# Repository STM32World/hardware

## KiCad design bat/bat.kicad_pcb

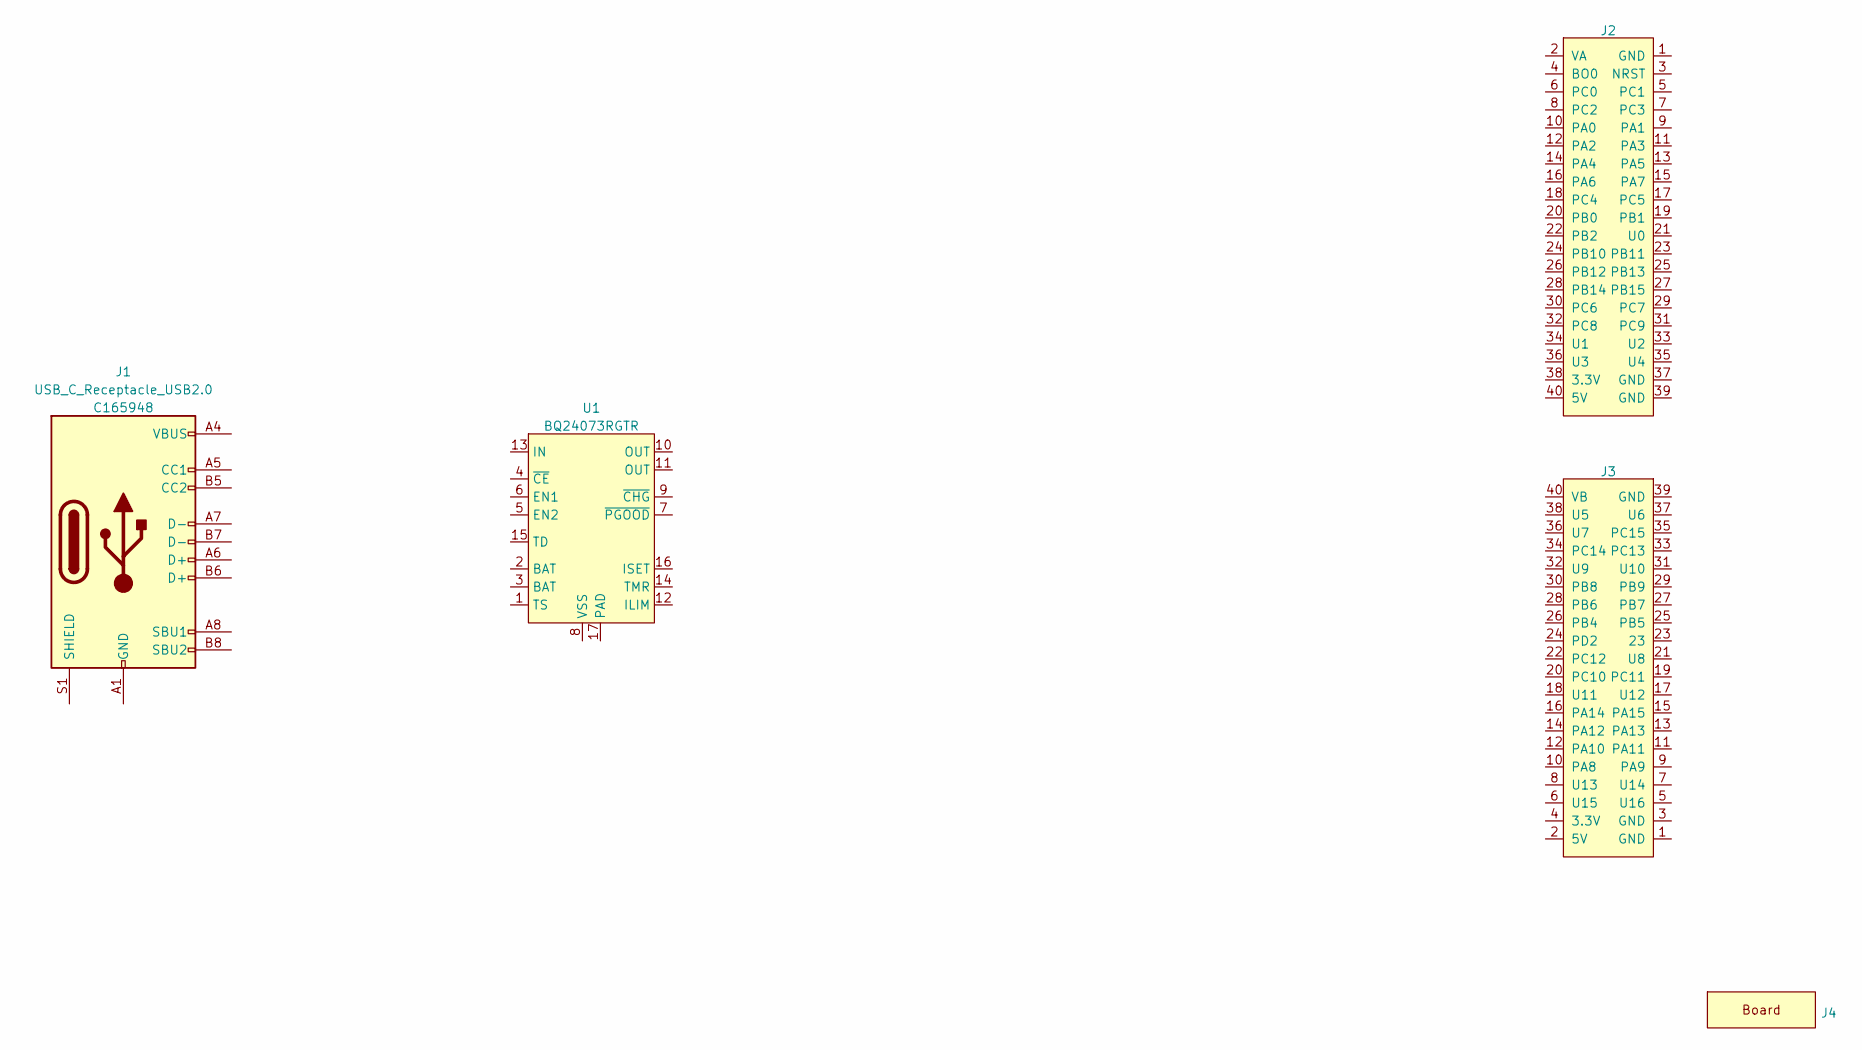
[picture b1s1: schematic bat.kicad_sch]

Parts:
J1: USB_C_Receptacle_USB2.0; USB_C_Receptacle_HRO_TYPE-C-31-M-12; LCSC C165948
J2: STM32WORLD_CONNECTOR_1; PinSocket_2x20_P2.54mm_Vertical_Stackable; LCSC C35165
J3: STM32WORLD_CONNECTOR_2; PinSocket_2x20_P2.54mm_Vertical_Stackable; LCSC C35165
J4: STM32WORLD_BOARD
U1: BQ24073RGTR; QFN-16-1EP_3x3mm_P0.5mm_EP1.7x1.7mm; LCSC C15220

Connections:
unnamed: J1.A1 (GND), J1.A12 (GND), J1.B1 (GND), J1.B12 (GND)
unnamed: J1.A4 (VBUS), J1.A9 (VBUS), J1.B4 (VBUS), J1.B9 (VBUS)

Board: 2 copper layers, 5 parts (0 on the bottom side), 2 nets, no tracks yet.

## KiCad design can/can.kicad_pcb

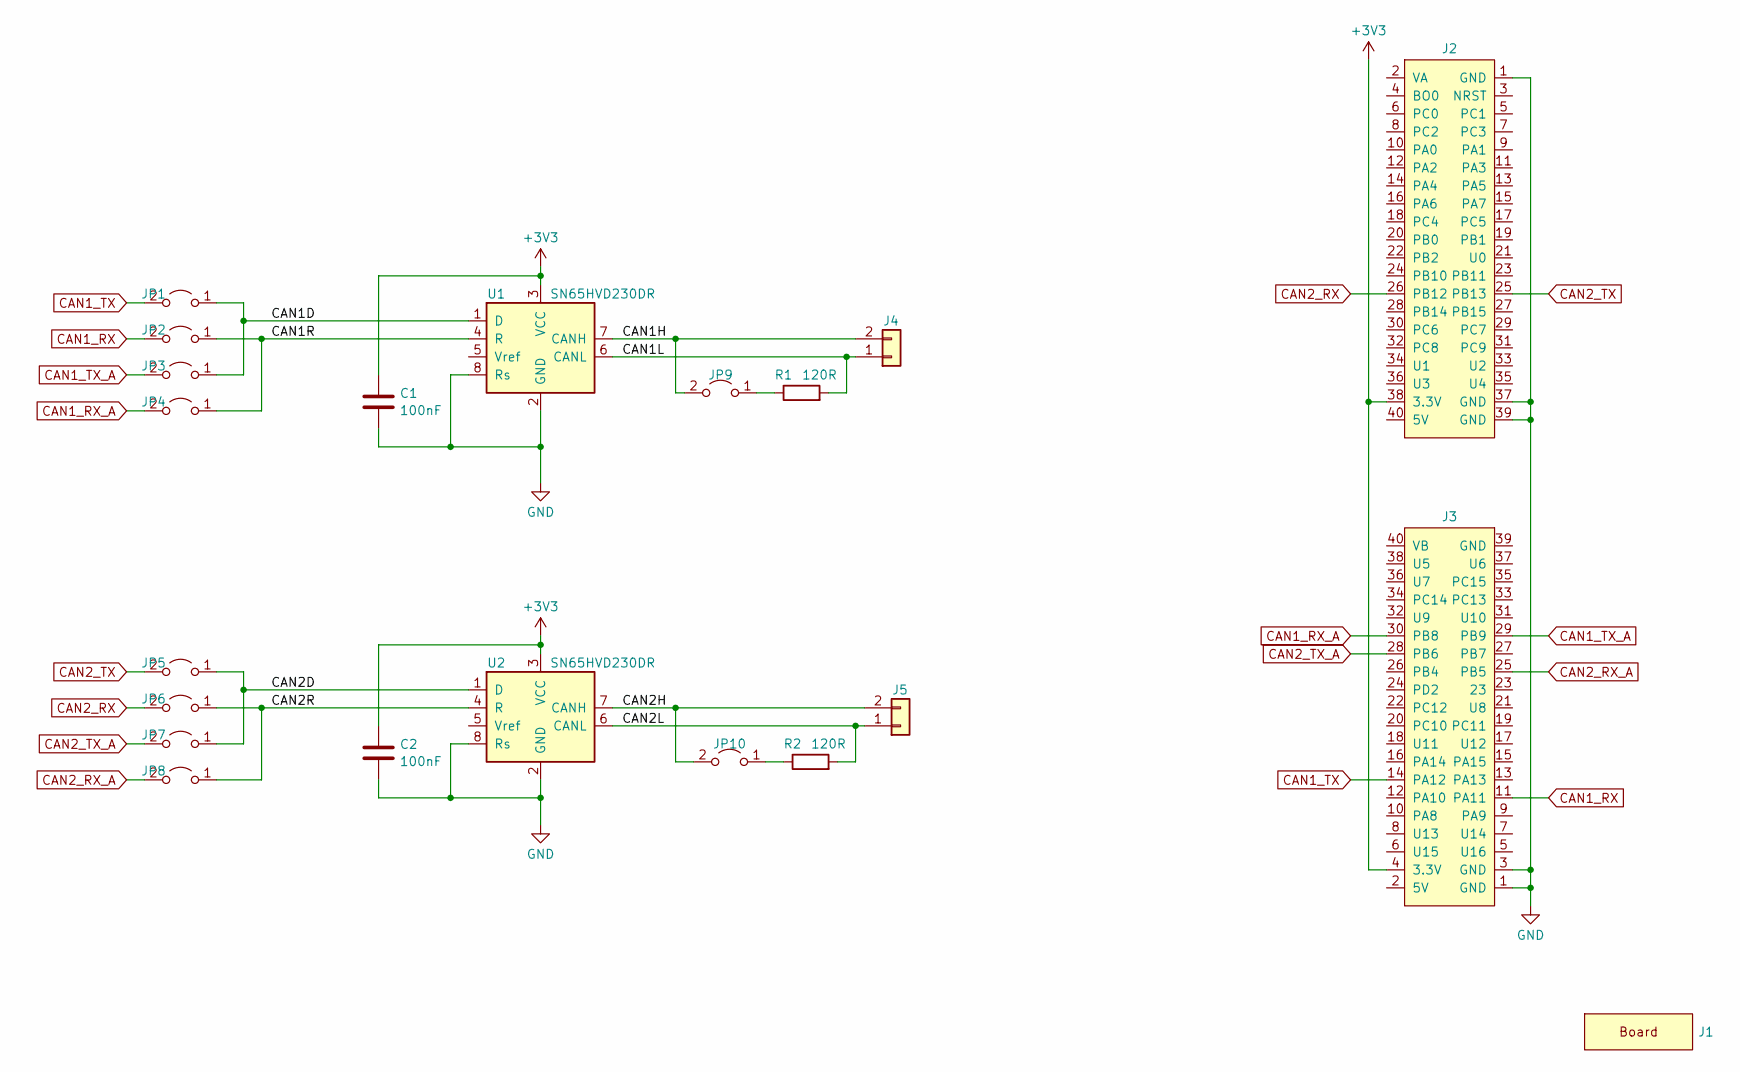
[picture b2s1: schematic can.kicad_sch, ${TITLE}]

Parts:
C1, C2: 100nF; C_0603_1608Metric; LCSC C14663
J1: STM32WORLD_BOARD
J2: STM32WORLD_CONNECTOR_1; PinSocket_2x20_P2.54mm_Vertical_Stackable; LCSC C35165
J3: STM32WORLD_CONNECTOR_2; PinSocket_2x20_P2.54mm_Vertical_Stackable; LCSC C35165
J4, J5: TerminalBlock_Phoenix_PT-1,5-2-5.0-H_1x02_P5.00mm_Horizontal
JP1, JP2, JP3, JP4, JP5, JP6, JP7, JP8, JP9, JP10: SolderJumper-2_P1.3mm_Open_TrianglePad1.0x1.5mm
R1, R2: 120R; R_0603_1608Metric; LCSC C22787
U1, U2: SN65HVD230DR; SOIC-8_3.9x4.9mm_P1.27mm; LCSC C12084

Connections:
+3V3: C1.1, C2.1, J2.38 (3.3V), J3.4 (3.3V), U1.3 (VCC), U2.3 (VCC)
/CAN1D: JP1.1 (A), JP3.1 (A), U1.1 (D)
/CAN1H: J4.2, JP9.2 (B), U1.7 (CANH)
/CAN1L: J4.1, R1.2, U1.6 (CANL)
/CAN1R: JP2.1 (A), JP4.1 (A), U1.4 (R)
/CAN2D: JP5.1 (A), JP7.1 (A), U2.1 (D)
/CAN2H: J5.2, JP10.2 (B), U2.7 (CANH)
/CAN2L: J5.1, R2.2, U2.6 (CANL)
/CAN2R: JP6.1 (A), JP8.1 (A), U2.4 (R)
CAN1_RX: J3.11 (PA11), JP2.2 (B)
CAN1_RX_A: J3.30 (PB8), JP4.2 (B)
CAN1_TX: J3.14 (PA12), JP1.2 (B)
CAN1_TX_A: J3.29 (PB9), JP3.2 (B)
CAN2_RX: J2.26 (PB12), JP6.2 (B)
CAN2_RX_A: J3.25 (PB5), JP8.2 (B)
CAN2_TX: J2.25 (PB13), JP5.2 (B)
CAN2_TX_A: J3.28 (PB6), JP7.2 (B)
GND: C1.2, C2.2, J2.1 (GND), J2.37 (GND), J2.39 (GND), J3.1 (GND), J3.3 (GND), U1.2 (GND), U1.8 (Rs), U2.2 (GND), U2.8 (Rs)
unnamed: JP9.1 (A), R1.1
unnamed: JP10.1 (A), R2.1

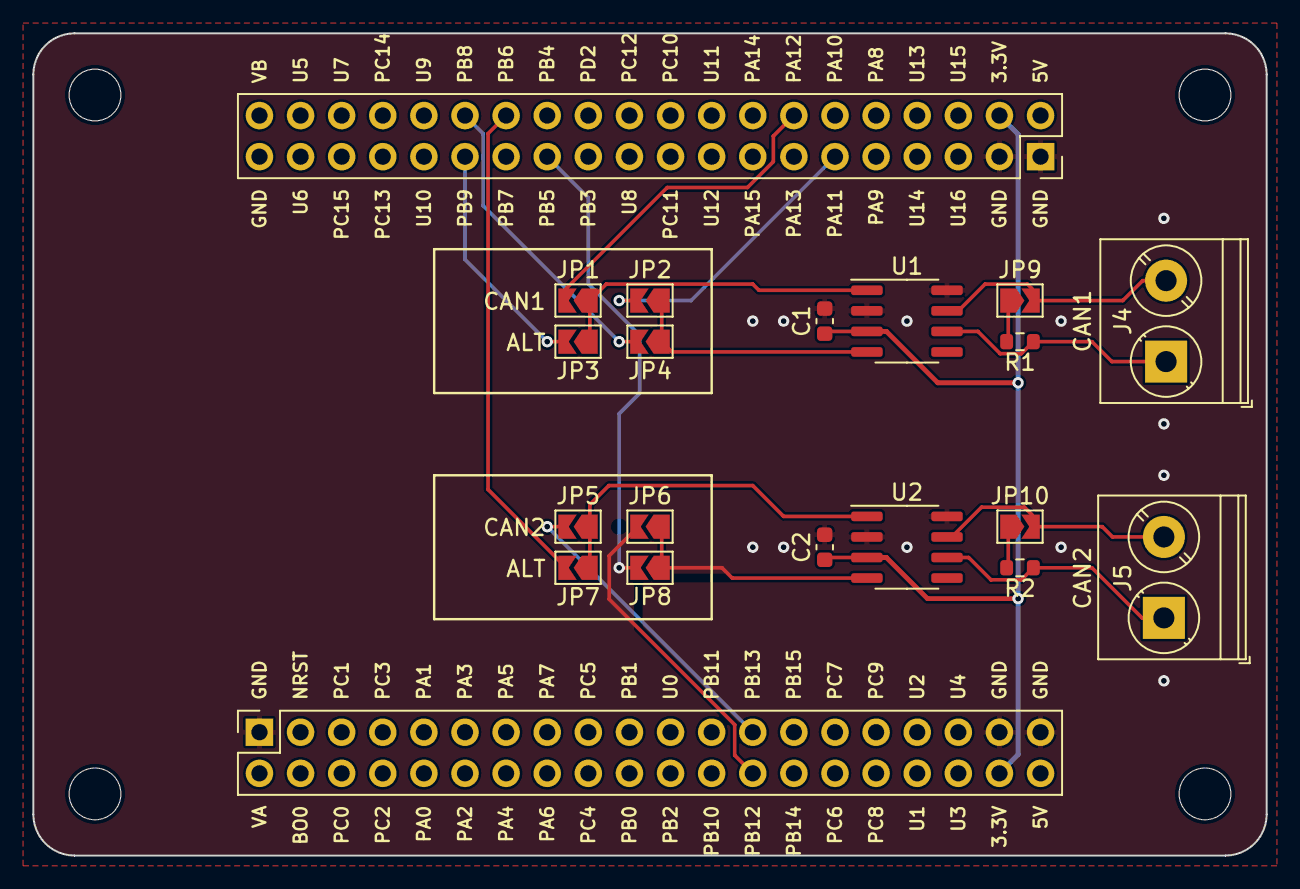
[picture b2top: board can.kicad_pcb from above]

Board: 2 copper layers, 76.2 x 50.8 mm, 21 parts (0 on the bottom side), 20 nets.

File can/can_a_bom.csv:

Comment,Designator,Footprint,LCSC
"100nF","C1,C2","Capacitor_SMD:C_0603_1608Metric","C14663"
"STM32WORLD_BOARD","J1","stm32world:STM32WORLD_BOARD"
"STM32WORLD_CONNECTOR_1","J2","stm32world:PinSocket_2x20_P2.54mm_Vertical_Stackable","C35165"
"STM32WORLD_CONNECTOR_2","J3","stm32world:PinSocket_2x20_P2.54mm_Vertical_Stackable","C35165"
"~","J4,J5","TerminalBlock_Phoenix:TerminalBlock_Phoenix_PT-1,5-2-5.0-H_1x02_P5.00mm_Horizontal"
"~","JP1,JP2,JP3,JP4,JP5,JP6,JP7,JP8,JP9,JP10","Jumper:SolderJumper-2_P1.3mm_Open_TrianglePad1.0x1.5mm"
"120R","R1,R2","Resistor_SMD:R_0603_1608Metric","C22787"
"SN65HVD230DR","U1,U2","Package_SO:SOIC-8_3.9x4.9mm_P1.27mm","C12084"

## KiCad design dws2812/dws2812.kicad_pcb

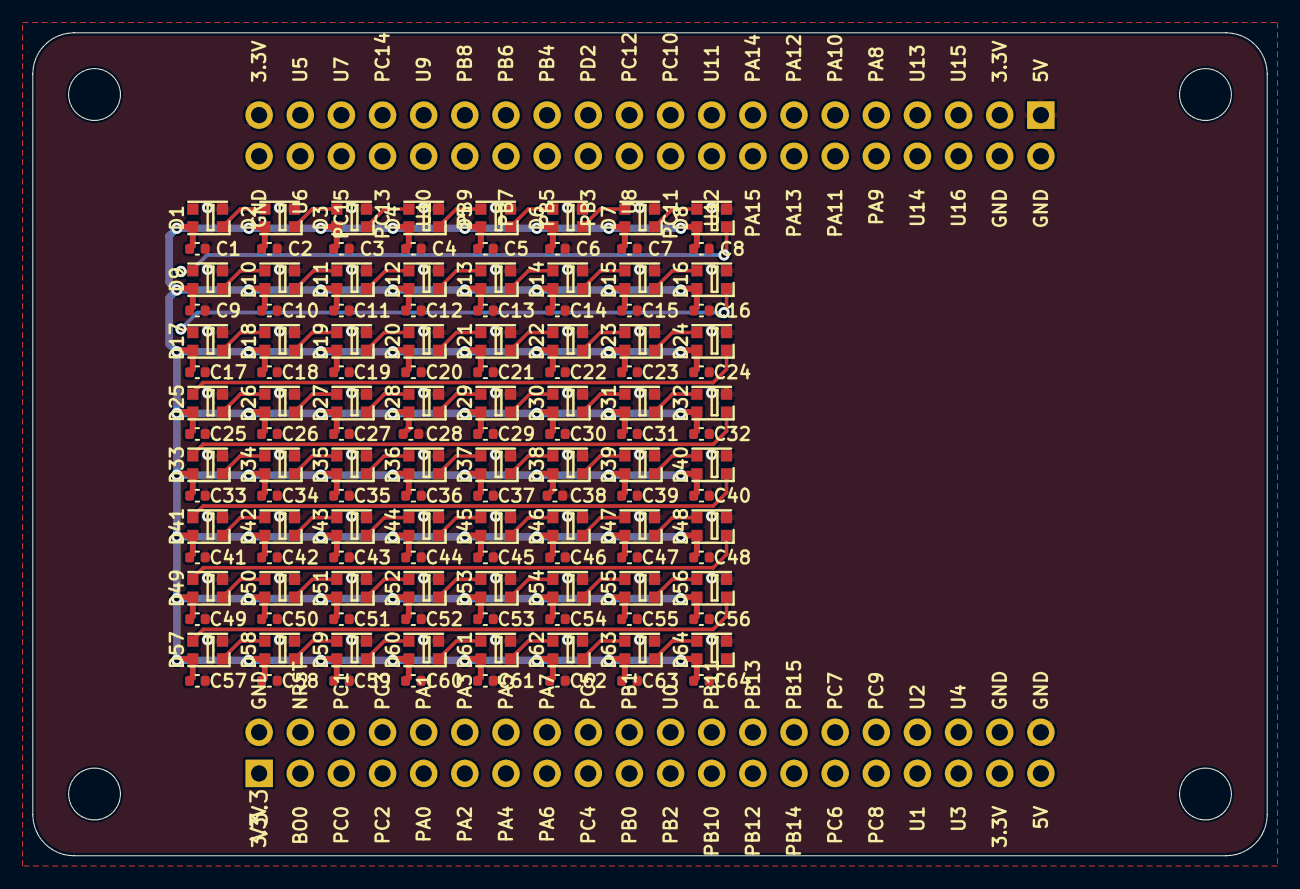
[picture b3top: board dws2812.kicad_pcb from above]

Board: 2 copper layers, 76.2 x 50.8 mm, 129 parts (0 on the bottom side), 65 nets.

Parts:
C1, C2, C3, C4, C5, C6, C7, C8, C9, C10, C11, C12, C13, C14, C15, C16, C17, C18, C19, C20, C21, C22, C23, C24, C25, C26, C27, C28, C29, C30, C31, C32, C33, C34, C35, C36, C37, C38, C39, C40, C41, C42, C43, C44, C45, C46, C47, C48, C49, C50, C51, C52, C53, C54, C55, C56, C57, C58, C59, C60, C61, C62, C63, C64: 100nF; C_0402_1005Metric
D1, D2, D3, D4, D5, D6, D7, D8, D9, D10, D11, D12, D13, D14, D15, D16, D17, D18, D19, D20, D21, D22, D23, D24, D25, D26, D27, D28, D29, D30, D31, D32, D33, D34, D35, D36, D37, D38, D39, D40, D41, D42, D43, D44, D45, D46, D47, D48, D49, D50, D51, D52, D53, D54, D55, D56, D57, D58, D59, D60, D61, D62, D63, D64: WS2812; LED_WS2812C-2020
J1: STM32WORLD_BASE

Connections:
+5V: C1.1, C2.1, C3.1, C4.1, C5.1, C6.1, C7.1, C8.1, C9.1, C10.1, C11.1, C12.1, C13.1, C14.1, C15.1, C16.1, C17.1, C18.1, C19.1, C20.1, C21.1, C22.1, C23.1, C24.1, C25.1, C26.1, C27.1, C28.1, C29.1, C30.1, C31.1, C32.1, C33.1, C34.1, C35.1, C36.1, C37.1, C38.1, C39.1, C40.1, C41.1, C42.1, C43.1, C44.1, C45.1, C46.1, C47.1, C48.1, C49.1, C50.1, C51.1, C52.1, C53.1, C54.1, C55.1, C56.1, C57.1, C58.1, C59.1, C60.1, C61.1, C62.1, C63.1, C64.1, D1.4, D2.4, D3.4, D4.4, D5.4, D6.4, D7.4, D8.4, D9.4, D10.4, D11.4, D12.4, D13.4, D14.4, D15.4, D16.4, D17.4, D18.4, D19.4, D20.4, D21.4, D22.4, D23.4, D24.4, D25.4, D26.4, D27.4, D28.4, D29.4, D30.4, D31.4, D32.4, D33.4, D34.4, D35.4, D36.4, D37.4, D38.4, D39.4, D40.4, D41.4, D42.4, D43.4, D44.4, D45.4, D46.4, D47.4, D48.4, D49.4, D50.4, D51.4, D52.4, D53.4, D54.4, D55.4, D56.4, D57.4, D58.4, D59.4, D60.4, D61.4, D62.4, D63.4, D64.4
GND: C1.2, C2.2, C3.2, C4.2, C5.2, C6.2, C7.2, C8.2, C9.2, C10.2, C11.2, C12.2, C13.2, C14.2, C15.2, C16.2, C17.2, C18.2, C19.2, C20.2, C21.2, C22.2, C23.2, C24.2, C25.2, C26.2, C27.2, C28.2, C29.2, C30.2, C31.2, C32.2, C33.2, C34.2, C35.2, C36.2, C37.2, C38.2, C39.2, C40.2, C41.2, C42.2, C43.2, C44.2, C45.2, C46.2, C47.2, C48.2, C49.2, C50.2, C51.2, C52.2, C53.2, C54.2, C55.2, C56.2, C57.2, C58.2, C59.2, C60.2, C61.2, C62.2, C63.2, C64.2, D1.2, D2.2, D3.2, D4.2, D5.2, D6.2, D7.2, D8.2, D9.2, D10.2, D11.2, D12.2, D13.2, D14.2, D15.2, D16.2, D17.2, D18.2, D19.2, D20.2, D21.2, D22.2, D23.2, D24.2, D25.2, D26.2, D27.2, D28.2, D29.2, D30.2, D31.2, D32.2, D33.2, D34.2, D35.2, D36.2, D37.2, D38.2, D39.2, D40.2, D41.2, D42.2, D43.2, D44.2, D45.2, D46.2, D47.2, D48.2, D49.2, D50.2, D51.2, D52.2, D53.2, D54.2, D55.2, D56.2, D57.2, D58.2, D59.2, D60.2, D61.2, D62.2, D63.2, D64.2, J1.2, J1.40, J1.41, J1.79
unnamed: D1.1, D2.3
unnamed: D2.1, D3.3
unnamed: D3.1, D4.3
unnamed: D4.1, D5.3
unnamed: D5.1, D6.3
unnamed: D6.1, D7.3
unnamed: D7.1, D8.3
unnamed: D8.1, D9.3
unnamed: D10.1, D11.3
unnamed: D9.1, D10.3
unnamed: D11.1, D12.3
unnamed: D12.1, D13.3
unnamed: D13.1, D14.3
unnamed: D14.1, D15.3
unnamed: D15.1, D16.3
unnamed: D16.1, D17.3
unnamed: D17.1, D18.3
unnamed: D18.1, D19.3
unnamed: D19.1, D20.3
unnamed: D20.1, D21.3
unnamed: D21.1, D22.3
unnamed: D22.1, D23.3
unnamed: D23.1, D24.3
unnamed: D24.1, D25.3
unnamed: D25.1, D26.3
unnamed: D26.1, D27.3
unnamed: D27.1, D28.3
unnamed: D28.1, D29.3
unnamed: D29.1, D30.3
unnamed: D30.1, D31.3
unnamed: D31.1, D32.3
unnamed: D32.1, D33.3
unnamed: D33.1, D34.3
unnamed: D34.1, D35.3
unnamed: D35.1, D36.3
unnamed: D36.1, D37.3
unnamed: D37.1, D38.3
unnamed: D38.1, D39.3
unnamed: D39.1, D40.3
unnamed: D40.1, D41.3
unnamed: D41.1, D42.3
unnamed: D42.1, D43.3
unnamed: D43.1, D44.3
unnamed: D44.1, D45.3
unnamed: D45.1, D46.3
unnamed: D46.1, D47.3
unnamed: D47.1, D48.3
unnamed: D48.1, D49.3
unnamed: D49.1, D50.3
unnamed: D50.1, D51.3
unnamed: D51.1, D52.3
unnamed: D52.1, D53.3
unnamed: D53.1, D54.3
unnamed: D54.1, D55.3
unnamed: D55.1, D56.3
unnamed: D56.1, D57.3
unnamed: D57.1, D58.3
unnamed: D58.1, D59.3
unnamed: D59.1, D60.3
unnamed: D60.1, D61.3
unnamed: D61.1, D62.3
unnamed: D62.1, D63.3
unnamed: D63.1, D64.3

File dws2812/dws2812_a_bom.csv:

Comment,Designator,Footprint,LCSC
"100nF","C1,C2,C3,C4,C5,C6,C7,C8,C9,C10,C11,C12,C13,C14,C15,C16,C17,C18,C19,C20,C21,C22,C23,C24,C25,C26,C27,C28,C29,C30,C31,C32,C33,C34,C35,C36,C37,C38,C39,C40,C41,C42,C43,C44,C45,C46,C47,C48,C49,C50,C51,C52,C53,C54,C55,C56,C57,C58,C59,C60,C61,C62,C63,C64","Capacitor_SMD:C_0402_1005Metric","C1525"
"WS2812","D1,D2,D3,D4,D5,D6,D7,D8,D9,D10,D11,D12,D13,D14,D15,D16,D17,D18,D19,D20,D21,D22,D23,D24,D25,D26,D27,D28,D29,D30,D31,D32,D33,D34,D35,D36,D37,D38,D39,D40,D41,D42,D43,D44,D45,D46,D47,D48,D49,D50,D51,D52,D53,D54,D55,D56,D57,D58,D59,D60,D61,D62,D63,D64","stm32world:LED_WS2812C-2020","C965556"
"STM32WORLD_BASE","J1","stm32world:STM32WORLD_BASE"

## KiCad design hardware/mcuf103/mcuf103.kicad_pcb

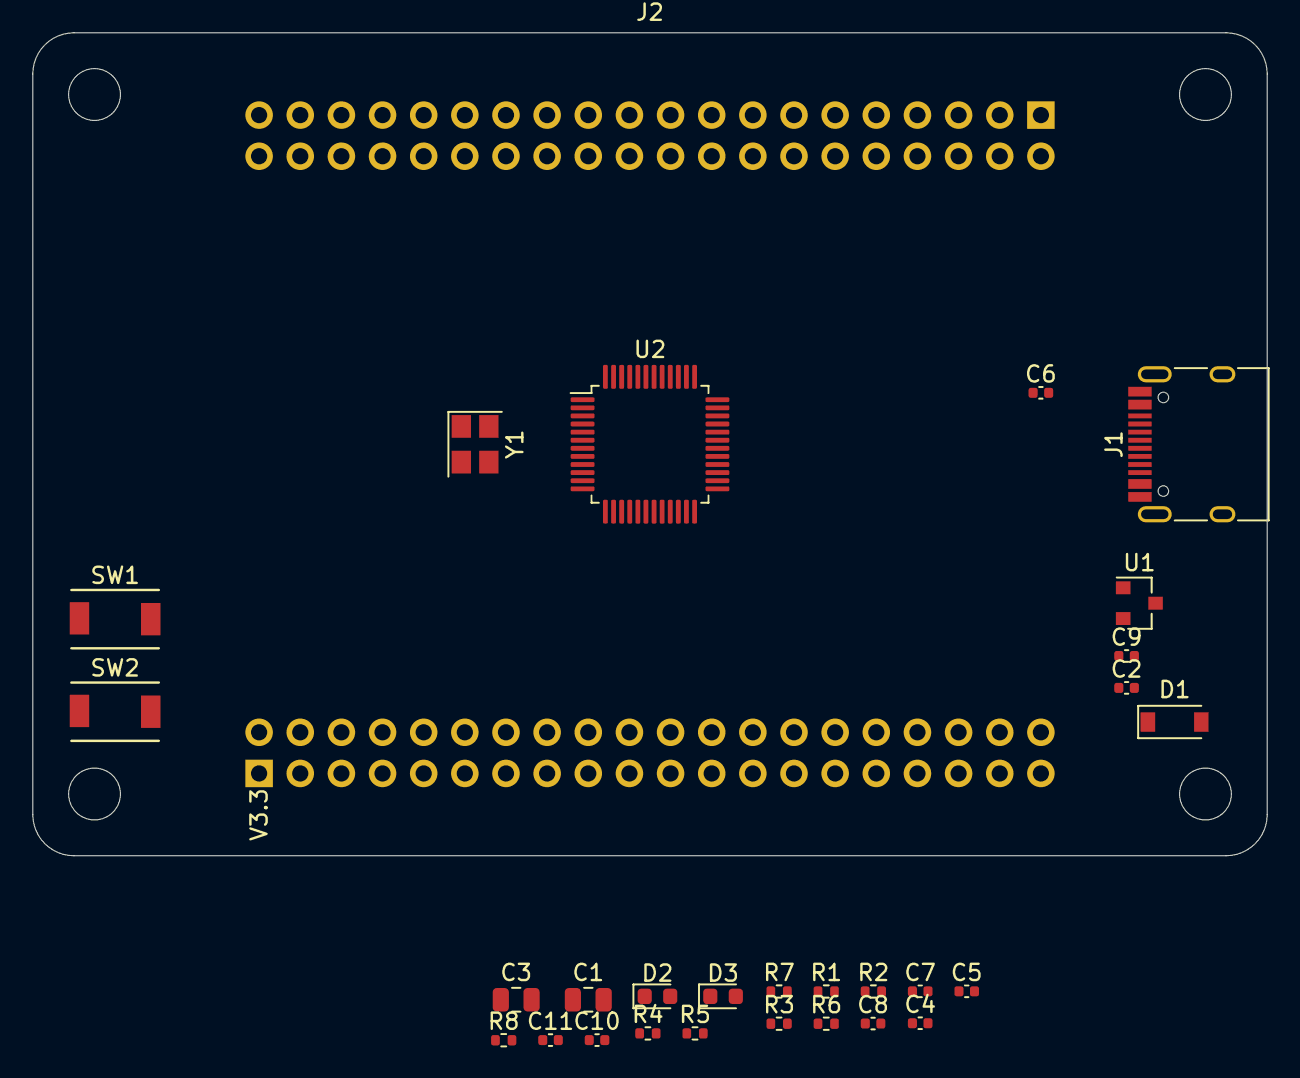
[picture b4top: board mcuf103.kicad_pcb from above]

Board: 2 copper layers, 76.2 x 50.8 mm, 29 parts (0 on the bottom side), 50 nets, no tracks yet.

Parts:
C1, C3: 10uF; C_0805_2012Metric
C2, C5, C6, C7, C8: 100nF; C_0402_1005Metric
C4: 1uF; C_0402_1005Metric
C9: 10nF; C_0402_1005Metric
C10, C11: 20pF; C_0402_1005Metric
D1: D_SOD-123
D2: GR; LED_0603_1608Metric
D3: BLUE; LED_0603_1608Metric
J1: USB_C_Receptacle_HRO_TYPE-C-31-M-12
J2: STM32WORLD_BASE
R1, R2: 10k; R_0402_1005Metric
R3, R4: 5.1k; R_0402_1005Metric
R5, R6: 22R; R_0402_1005Metric
R7, R8: 220; R_0402_1005Metric
SW1, SW2: TS-1088R-02526
U1: XC6206P332MR; SOT-23
U2: STM32F103CBTx; LQFP-48_7x7mm_P0.5mm
Y1: 16 MHz; Crystal_SMD_3225-4Pin_3.2x2.5mm

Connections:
+3V3: C3.1, C4.1, C5.1, C6.1, C7.1, C8.1, C9.1, D2.2, D3.2, J2.1, J2.39, J2.41, J2.79, R1.1, SW2.2, U1.2, U2.1, U2.9, U2.24, U2.36, U2.48
+5V: C1.1, D1.1, U1.3
BO0: J2.3, R2.1, SW2.1, U2.44
GND: C1.2, C2.2, C3.2, C4.2, C5.2, C6.2, C7.2, C8.2, C9.2, C10.2, C11.2, J1.A1, J1.A12, J1.B1, J1.B12, J1.S1, J2.2, J2.40, J2.42, J2.80, R2.2, R7.2, SW1.1, U1.1, U2.8, U2.23, U2.35, U2.47, Y1.2, Y1.4
NRST: C2.1, J2.4, R1.2, SW1.2, U2.7
unnamed: C10.1, U2.5, Y1.1
unnamed: C11.1, U2.6, Y1.3
unnamed: D2.1, R7.1
unnamed: D3.1, R8.1
unnamed: J1.A5, R3.1
unnamed: J1.A6, J1.B6, R6.1
unnamed: J1.A7, J1.B7, R5.1
unnamed: J1.B5, R4.1
PA0: J2.9, U2.10
PA1: J2.10, U2.11
PA2: J2.11, U2.12
PA3: J2.12, U2.13
PA4: J2.13, U2.14
PA5: J2.14, U2.15
PA6: J2.15, U2.16
PA7: J2.16, U2.17
PA8: J2.49, U2.29
PA9: J2.50, U2.30
PA10: J2.51, U2.31
PA11: J2.52, R5.2, U2.32
PA12: J2.53, R6.2, U2.33
PA13: J2.54, U2.34
PA14: J2.55, U2.37
PA15: J2.56, U2.38
PB0: J2.19, U2.18
PB1: J2.20, U2.19
PB2: J2.21, U2.20
PB3: J2.64, U2.39
PB4: J2.65, U2.40
PB5: J2.66, U2.41
PB6: J2.67, U2.42
PB7: J2.68, U2.43
PB8: J2.69, U2.45
PB9: J2.70, U2.46
PB10: J2.23, U2.21
PB11: J2.24, U2.22
PB12: J2.25, U2.25
PB13: J2.26, U2.26
PB14: J2.27, U2.27
PB15: J2.28, U2.28
PC13: J2.74, R8.2, U2.2
PC14: J2.73, U2.3
PC15: J2.76, U2.4
UCC: R3.2, R4.2
VBUS: D1.2, J1.A4, J1.A9, J1.B4, J1.B9

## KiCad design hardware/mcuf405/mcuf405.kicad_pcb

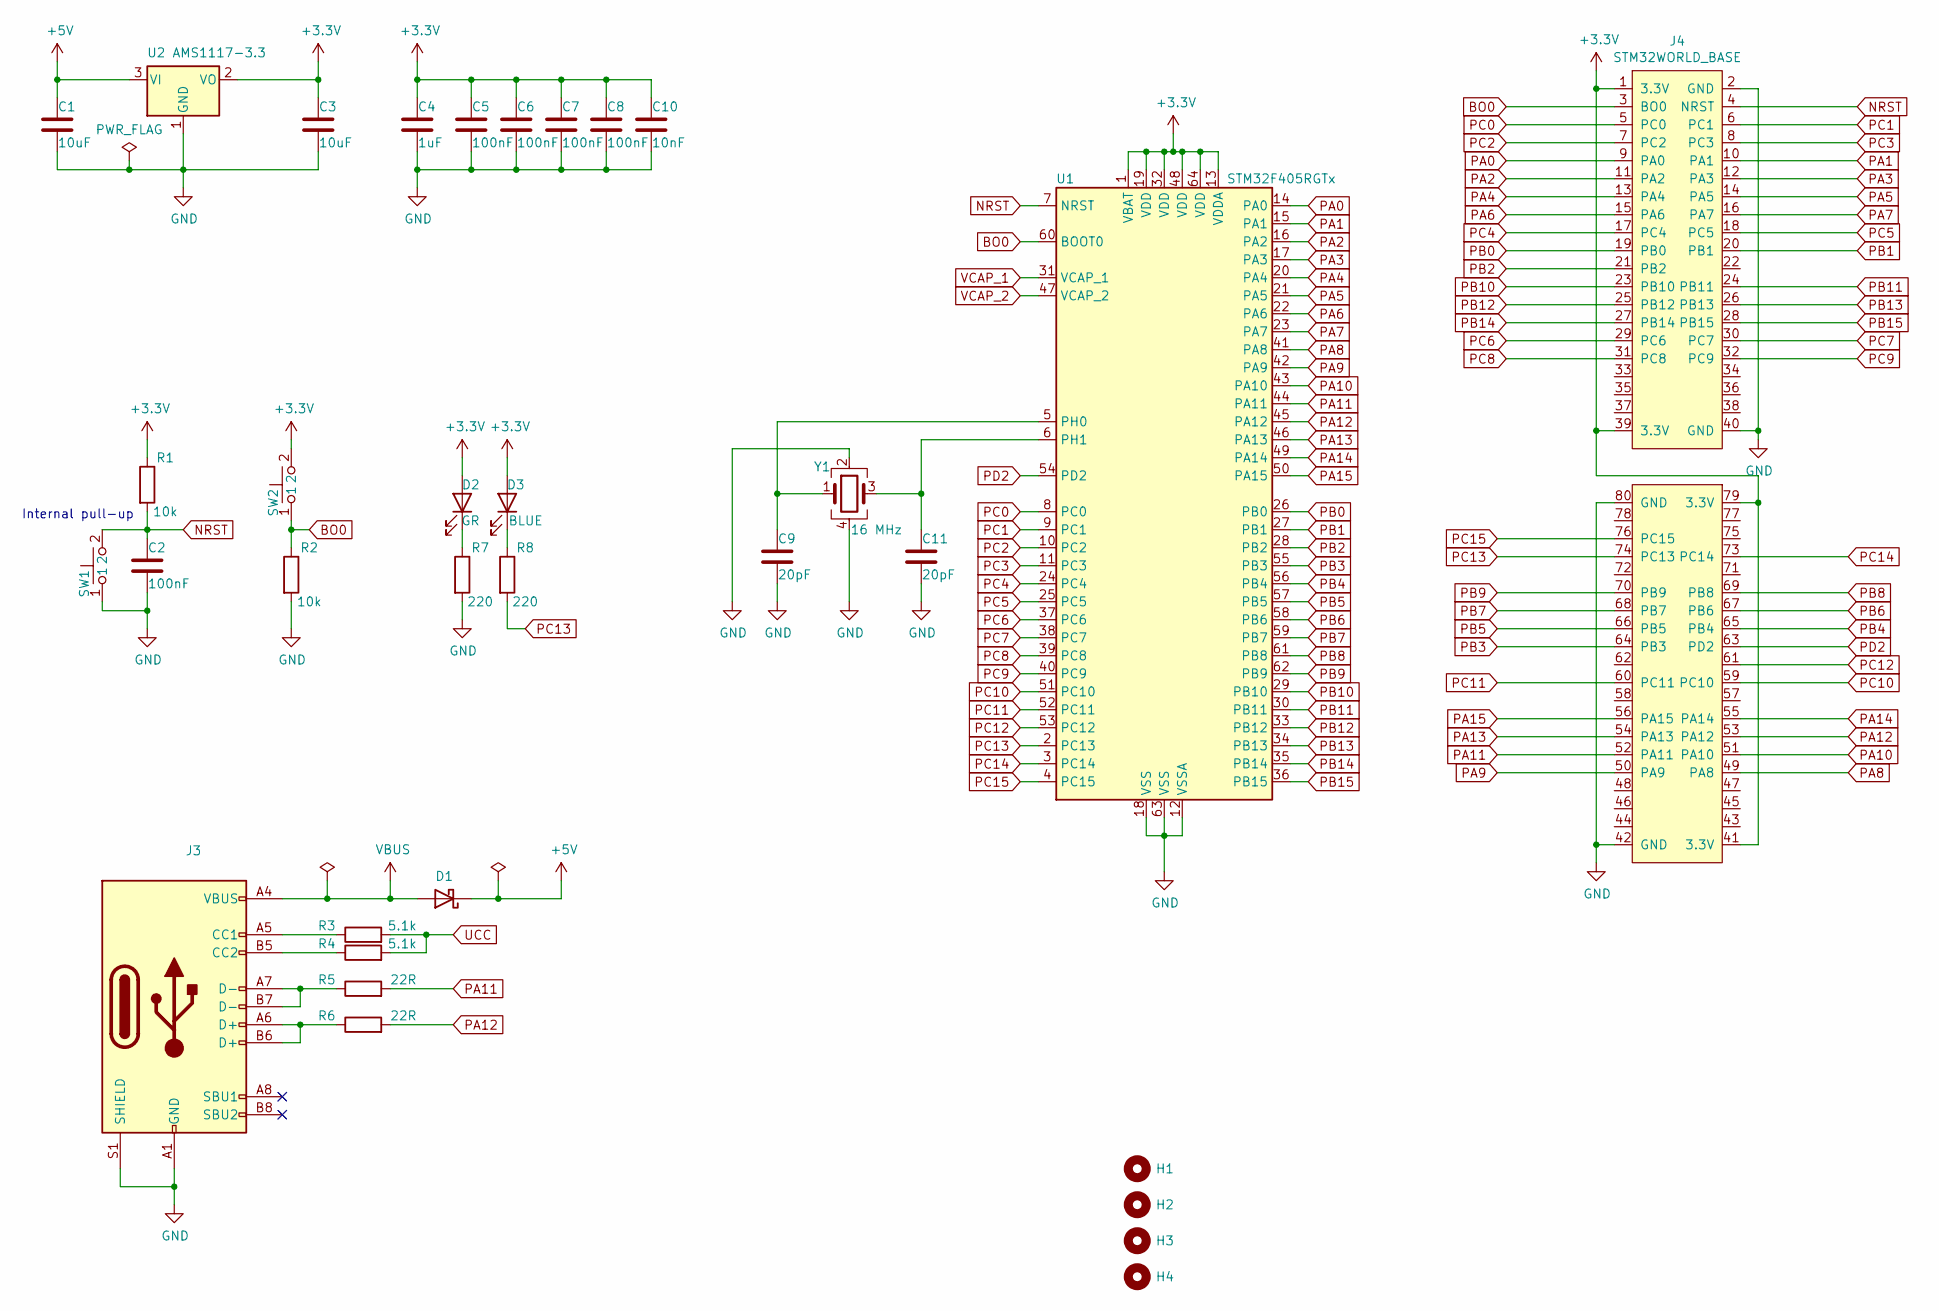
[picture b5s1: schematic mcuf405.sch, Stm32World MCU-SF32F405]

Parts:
C1, C3: 10uF; C_0805_2012Metric; LCSC C15850
C2: 100nF; C_0402_1005Metric; LCSC C1525
C4: 1uF; C_0402_1005Metric; LCSC C52923
C5, C6, C7, C8: C_100NF_0603; C_0603_1608Metric; LCSC C14663
C9, C11: 20pF; C_0402_1005Metric; LCSC C1554
C10: 10nF; C_0402_1005Metric; LCSC C15195
D1: D_SOD-123; LCSC C8598
D2: GR; LED_0603_1608Metric; LCSC C72043
D3: BLUE; LED_0603_1608Metric; LCSC C72041
H1, H2, H3, H4: MountingHole_3.2mm_M3
J3: USB_C_Receptacle_HRO_TYPE-C-31-M-12; LCSC C165948
J4: STM32WORLD_BASE
R1, R2: 10k; R_0402_1005Metric; LCSC C25531
R3, R4: 5.1k; R_0402_1005Metric; LCSC C25905
R5, R6: 22R; R_0402_1005Metric; LCSC C25092
R7, R8: 220; R_0402_1005Metric; LCSC C25091
SW1, SW2: TS-1088R-02526; LCSC C455281
U1: STM32F405RGTx; LQFP-64_10x10mm_P0.5mm
U2: AMS1117-3.3; SOT-223-3_TabPin2; LCSC C6186
Y1: 16 MHz; Crystal_SMD_3225-4Pin_3.2x2.5mm; LCSC C13738

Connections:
+3V3: C3.1, C4.1, C5.1, C6.1, C7.1, C8.1, C10.1, D2.2 (A), D3.2 (A), J4.1 (3.3V), J4.39 (3.3V), J4.41 (3.3V), J4.79 (3.3V), R1.1, SW2.2, U1.1 (VBAT), U1.13 (VDDA), U1.19 (VDD), U1.32 (VDD), U1.48 (VDD), U1.64 (VDD), U2.2 (VO)
+5V: C1.1, D1.1 (K), U2.3 (VI)
BO0: J4.3 (BO0), R2.1, SW2.1, U1.60 (BOOT0)
GND: C1.2, C2.2, C3.2, C4.2, C5.2, C6.2, C7.2, C8.2, C9.2, C10.2, C11.2, J3.A1 (GND), J3.A12 (GND), J3.B1 (GND), J3.B12 (GND), J3.S1 (SHIELD), J4.2 (GND), J4.40 (GND), J4.42 (GND), J4.80 (GND), R2.2, R7.2, SW1.1, U1.12 (VSSA), U1.18 (VSS), U1.63 (VSS), U2.1 (GND), Y1.2, Y1.4
NRST: C2.1, J4.4 (NRST), R1.2, SW1.2, U1.7 (NRST)
unnamed: C9.1, U1.5 (PH0), Y1.1
unnamed: C11.1, U1.6 (PH1), Y1.3
unnamed: D2.1 (K), R7.1
unnamed: D3.1 (K), R8.1
unnamed: J3.A5 (CC1), R3.1
unnamed: J3.A6 (D+), J3.B6 (D+), R6.1
unnamed: J3.A7 (D-), J3.B7 (D-), R5.1
unnamed: J3.B5 (CC2), R4.1
PA0: J4.9 (PA0), U1.14 (PA0)
PA1: J4.10 (PA1), U1.15 (PA1)
PA2: J4.11 (PA2), U1.16 (PA2)
PA3: J4.12 (PA3), U1.17 (PA3)
PA4: J4.13 (PA4), U1.20 (PA4)
PA5: J4.14 (PA5), U1.21 (PA5)
PA6: J4.15 (PA6), U1.22 (PA6)
PA7: J4.16 (PA7), U1.23 (PA7)
PA8: J4.49 (PA8), U1.41 (PA8)
PA9: J4.50 (PA9), U1.42 (PA9)
PA10: J4.51 (PA10), U1.43 (PA10)
PA11: J4.52 (PA11), R5.2, U1.44 (PA11)
PA12: J4.53 (PA12), R6.2, U1.45 (PA12)
PA13: J4.54 (PA13), U1.46 (PA13)
PA14: J4.55 (PA14), U1.49 (PA14)
PA15: J4.56 (PA15), U1.50 (PA15)
PB0: J4.19 (PB0), U1.26 (PB0)
PB1: J4.20 (PB1), U1.27 (PB1)
PB2: J4.21 (PB2), U1.28 (PB2)
PB3: J4.64 (PB3), U1.55 (PB3)
PB4: J4.65 (PB4), U1.56 (PB4)
PB5: J4.66 (PB5), U1.57 (PB5)
PB6: J4.67 (PB6), U1.58 (PB6)
PB7: J4.68 (PB7), U1.59 (PB7)
PB8: J4.69 (PB8), U1.61 (PB8)
PB9: J4.70 (PB9), U1.62 (PB9)
PB10: J4.23 (PB10), U1.29 (PB10)
PB11: J4.24 (PB11), U1.30 (PB11)
PB12: J4.25 (PB12), U1.33 (PB12)
PB13: J4.26 (PB13), U1.34 (PB13)
PB14: J4.27 (PB14), U1.35 (PB14)
PB15: J4.28 (PB15), U1.36 (PB15)
PC0: J4.5 (PC0), U1.8 (PC0)
PC1: J4.6 (PC1), U1.9 (PC1)
PC2: J4.7 (PC2), U1.10 (PC2)
PC3: J4.8 (PC3), U1.11 (PC3)
PC4: J4.17 (PC4), U1.24 (PC4)
PC5: J4.18 (PC5), U1.25 (PC5)
PC6: J4.29 (PC6), U1.37 (PC6)
PC7: J4.30 (PC7), U1.38 (PC7)
PC8: J4.31 (PC8), U1.39 (PC8)
PC9: J4.32 (PC9), U1.40 (PC9)
PC10: J4.59 (PC10), U1.51 (PC10)
PC11: J4.60 (PC11), U1.52 (PC11)
PC12: J4.61, U1.53 (PC12)
PC13: J4.74 (PC13), R8.2, U1.2 (PC13)
PC14: J4.73 (PC14), U1.3 (PC14)
PC15: J4.76 (PC15), U1.4 (PC15)
PD2: J4.63 (PD2), U1.54 (PD2)
UCC: R3.2, R4.2
VBUS: D1.2 (A), J3.A4 (VBUS), J3.A9 (VBUS), J3.B4 (VBUS), J3.B9 (VBUS)
VCAP_1: U1.31 (VCAP_1)
VCAP_2: U1.47 (VCAP_2)

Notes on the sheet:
Internal pull-up

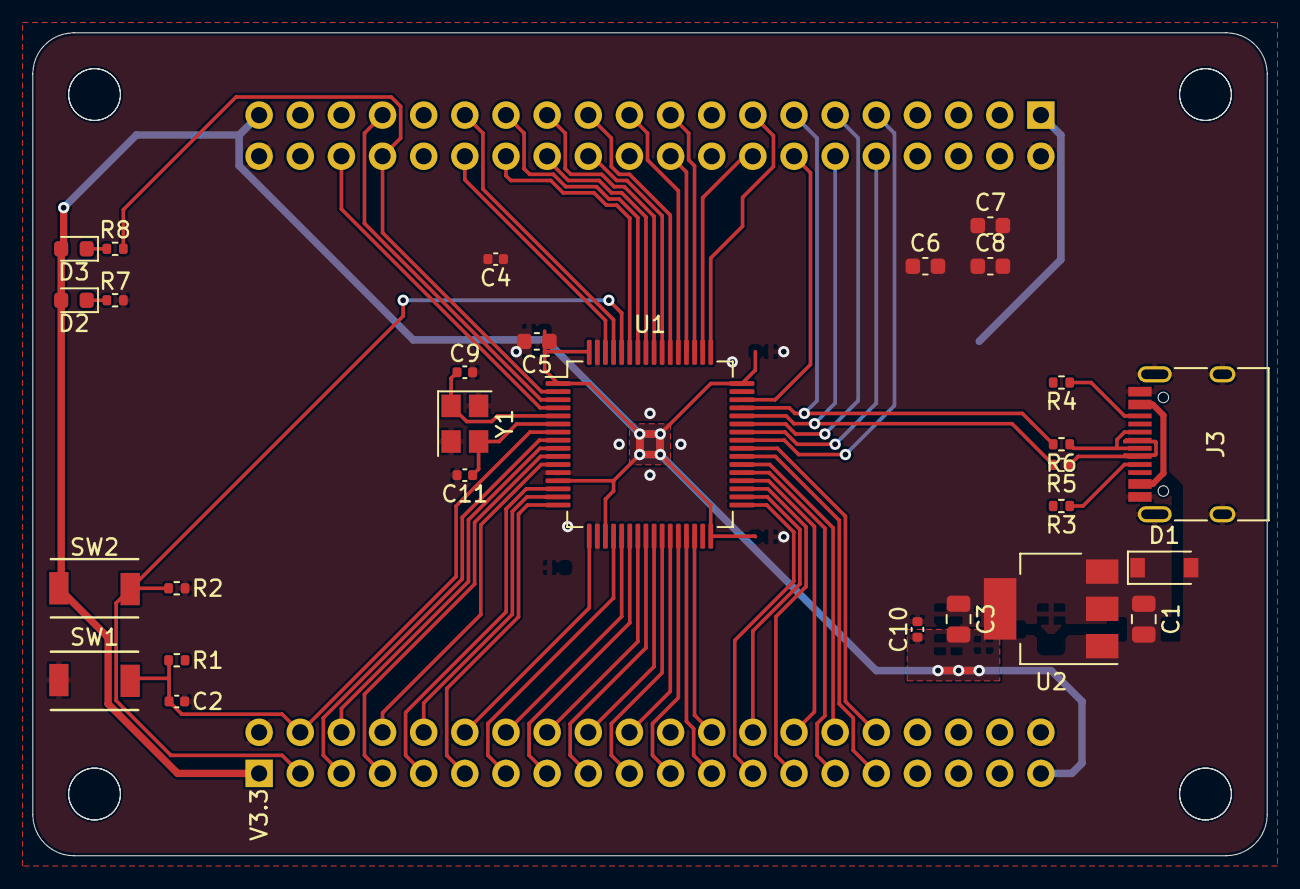
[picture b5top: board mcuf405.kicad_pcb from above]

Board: 2 copper layers, 76.2 x 50.8 mm, 33 parts (0 on the bottom side), 64 nets.

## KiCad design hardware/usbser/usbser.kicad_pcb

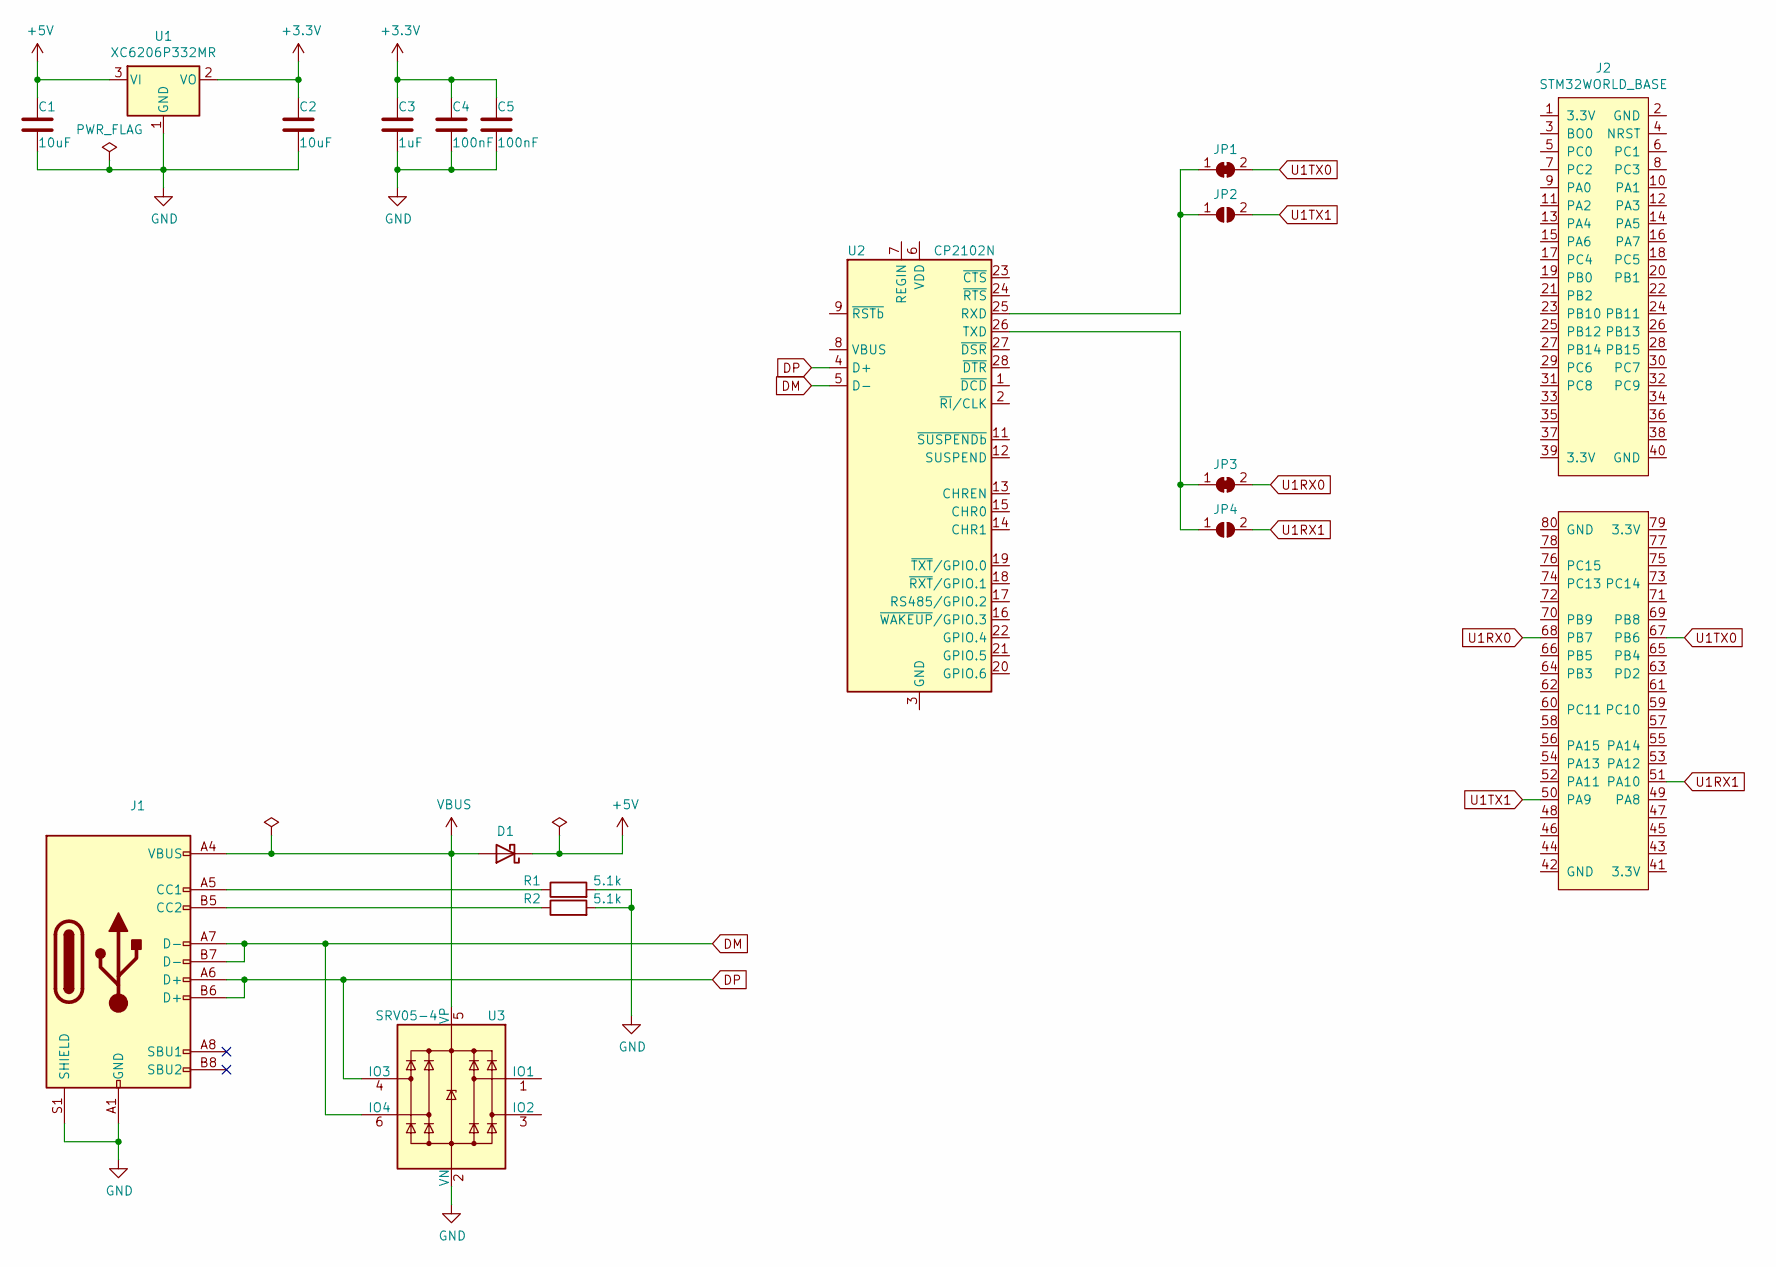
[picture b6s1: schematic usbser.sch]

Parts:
C1, C2: 10uF; C_0805_2012Metric; LCSC C15850
C3: 1uF; C_0402_1005Metric; LCSC C52923
C4, C5: 100nF; C_0402_1005Metric; LCSC C1525
D1: D_SOD-123; LCSC C8598
J1: USB_C_Receptacle_HRO_TYPE-C-31-M-12; LCSC C165948
J2: STM32WORLD_BASE
JP1, JP3: SolderJumper-2_P1.3mm_Bridged_Pad1.0x1.5mm
JP2, JP4: SolderJumper-2_P1.3mm_Open_Pad1.0x1.5mm
R1, R2: 5.1k; R_0402_1005Metric; LCSC C25905
U1: XC6206P332MR; SOT-23; LCSC C5446
U2: CP2102N; QFN-28-1EP_5x5mm_P0.5mm_EP3.35x3.35mm; LCSC C6568
U3: SRV05-4; SOT-23-6; LCSC C85364

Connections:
+3V3: C2.1, C3.1, C4.1, C5.1, U1.2 (VO)
+5V: C1.1, D1.1 (K), U1.3 (VI)
DM: J1.A7 (D-), J1.B7 (D-), U2.5 (D-), U3.6 (IO4)
DP: J1.A6 (D+), J1.B6 (D+), U2.4 (D+), U3.4 (IO3)
GND: C1.2, C2.2, C3.2, C4.2, C5.2, J1.A1 (GND), J1.A12 (GND), J1.B1 (GND), J1.B12 (GND), J1.S1 (SHIELD), R1.2, R2.2, U1.1 (GND), U3.2 (VN)
unnamed: J1.A5 (CC1), R1.1
unnamed: J1.B5 (CC2), R2.1
unnamed: JP1.1 (A), JP2.1 (A), U2.25 (RXD)
unnamed: JP3.1 (A), JP4.1 (A), U2.26 (TXD)
unnamed: U2.3 (GND), U2.29 (GND)
U1RX0: J2.68 (PB7), JP3.2 (B)
U1RX1: J2.51 (PA10), JP4.2 (B)
U1TX0: J2.67 (PB6), JP1.2 (B)
U1TX1: J2.50 (PA9), JP2.2 (B)
VBUS: D1.2 (A), J1.A4 (VBUS), J1.A9 (VBUS), J1.B4 (VBUS), J1.B9 (VBUS), U3.5 (VP)

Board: 2 copper layers, 17 parts (0 on the bottom side), 15 nets, no tracks yet.
